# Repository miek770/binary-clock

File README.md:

# Binary Clock

This is a simple binary clock project using a PIC18F2220, pretty much for:

1. The fun of it;
2. Getting more experience with Eagle PCB design;
3. Doing a first PIC C project (I've only programmed PICs in assembly before).

The clamp on the right is there to hold down the buttons (hidden) while the glue dries up. More pictures in [media](https://github.com/miek770/binary-clock/tree/master/media)!

## To Do List

- Adjust timing to account for the cycles it takes for the time update and LED syncing. I noted an about 10 minutes drift over 24 hours, but I didn't take precise measurements at the beginning of the cycle. I just took another picture with my PC clock showing the seconds and the binary clock, and will compare the difference in at least 24 hours. I could also double-check by calculating the amount of cycles required for the interrupt subroutine;
    - Edit: This explaination is wrong; the timer doesn't stop counting while the ISR executes. I think the problem may be that I skip a "beat" because the ISR sometimes lasts longer than TMR0's 256 cycles counter. I'll see if the drift matches this assumption after a day.
- Test the low charge detection;
- Consider using delays.h instead of timer1 for the low-battery blink. The use of the timer seems unecessary and it would be a good excuse to explore the available functions;
- Consider importing timers.h to setup timer0, instead of manually setting each register;
- Consider using the idle power management mode when nothing is happening to reduce battery consumption. First check if it would interfere with timer0;

## Appearance

### Display

The clock uses 5 LEDs (bits) for the hours (24h format), 6 for the minutes and 6 for the seconds. Showing fractions of seconds seemed excessive.

## Supply

It can be fed either or by both:

1. 3x AA batteries;
2. A micro-USB port.

### Low Charge Detection

Both supplies are paralleled with diodes, and the PIC monitors the batteries' voltage so that an alarm (blinking LED) is raised when the batteries are low. For 1.5V AA batteries, this would be pretty much when they get under 1V. AN0 is used on the PIC to measure the battery voltage.

Hum thinking about it makes me realize that the voltage reference is Vdd. So if we ignore the voltage drop through the diode, which is gonna be constant, the voltage drop at the battery (with no USB supply) is going to drop proportionally with Vdd which means the AN0 measurement won't pick it up. Unless I use the voltage drop across the diode as a reference. At 4.5V at the batteries, with a 0.7V drop through the diode I'll get 3.8V at Vdd. When the batteries get to 3V (1V per cell), Vdd will equal 2.3V.

So Vbatt/Vdd = 4.5V/3.8V (1.184) at full charge, and 3V/2.3V (1.304) at low charge. Using a 50/50 voltage divider between Vbatt and AN0, the ratios would be 0.592 (full) and 0.652 (low). With a 10-bit A/D converter I have a 1024 resolution, which would be able to measure this. Basically the reading is going to go from 0/1023 to 1023/1023. A 0.592 ratio (full) would be read as 606 and a 0.652 ratio (low) as 667. So I could then consider any reading over 666 (0b1010011010) as a low battery charge.

This will need to be adjusted to account for the real diode voltage drop as well as the voltage divider ratio, but it should do the trick. For testing purposes I could use the time diodes to show the A/D conversion output. I have up to 17 bits (5+6+6 diodes).

## Timing

I switched from the PIC18F252 to the PIC18F2220 because the former doesn't have an internal oscillator. I assumed it did.

I will be using TMR0 to count seconds, using a bresenham algorithm as explained and implemented here: [http://www.romanblack.com/one_sec.htm](http://www.romanblack.com/one_sec.htm)

Basically (this is all from his website above):

    This next one is similar to the 1 second generators above. However it is optimised for speed and code space, because it uses a 16bit unsigned int variable for bres instead of a 32bit unsigned long. We do this by using values for the int period and the 1second period that are in the same ratio to each other, but smaller! We divide both values by 16;

    Optimised C code for a 1 second period with a 1MHz timer (4MHz xtal);

        // uses 1 variable; unsigned int bres
        // gets here every TMR0 int (every 256 ticks)

        bres += 16; // add (256/16) ticks to bresenham total

        if(bres >= 62500)   // if reached (1000000/16) 1 second!
        {
            bres -= 62500;  // subtract 1 second, retain error
            do_1sec_event();    // update clock, etc
        }

This is neat!

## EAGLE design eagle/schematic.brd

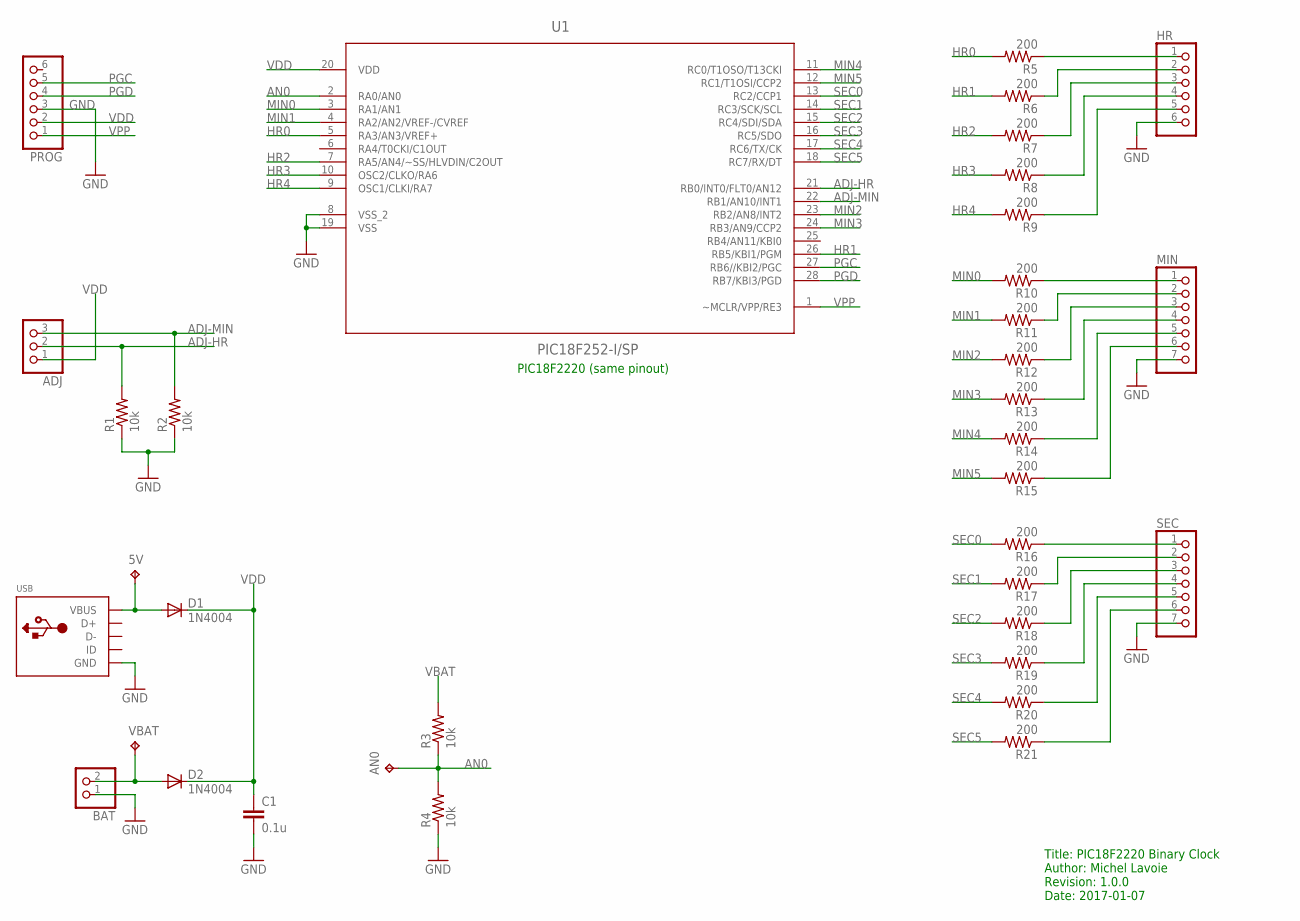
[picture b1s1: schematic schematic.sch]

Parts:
5V: TPPAD1-13; P1-13
ADJ: PINHD-1X3; 1X03
AN0: TPPAD1-13; P1-13
BAT: PINHD-1X2; 1X02
C1: 0.1u; CAP-PTH-SMALL-KIT
D1, D2: 1N4004; DO41-10
HR: PINHD-1X6; 1X06
MIN: PINHD-1X7; 1X07
PROG: PINHD-1X6; 1X06
R1, R2, R3, R4: 10k; AXIAL-0.3
R5, R6, R7, R8, R9, R10, R11, R12, R13, R14, R15, R16, R17, R18, R19, R20, R21: 200; AXIAL-0.3
SEC: PINHD-1X7; 1X07
U1: PIC18F252-I/SP; DIP254P762X508-28
USB: USBTHM; USB-MINIB-THM
VBAT: TPPAD1-13; P1-13

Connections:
5V: 5V.TP, D1.A, USB.VBUS
ADJ-HR: ADJ.2, R1.P$2 (2), U1.21 (RB0/INT0/FLT0/AN12)
ADJ-MIN: ADJ.3, R2.P$2 (2), U1.22 (RB1/AN10/INT1)
AN0: AN0.TP, R3.P$1 (1), R4.P$2 (2), U1.2 (RA0/AN0)
GND: BAT.1, C1.2, HR.6, MIN.7, PROG.3, R1.P$1 (1), R2.P$1 (1), R4.P$1 (1), SEC.7, U1.8 (VSS_2), U1.19 (VSS), USB.GND
HR0: R5.P$2 (2), U1.5 (RA3/AN3/VREF+)
HR1: R6.P$2 (2), U1.26 (RB5/KBI1/PGM)
HR2: R7.P$2 (2), U1.7 (RA5/AN4/~SS/HLVDIN/C2OUT)
HR3: R8.P$2 (2), U1.10 (OSC2/CLKO/RA6)
HR4: R9.P$2 (2), U1.9 (OSC1/CLKI/RA7)
MIN0: R10.P$2 (2), U1.3 (RA1/AN1)
MIN1: R11.P$2 (2), U1.4 (RA2/AN2/VREF-/CVREF)
MIN2: R12.P$2 (2), U1.23 (RB2/AN8/INT2)
MIN3: R13.P$2 (2), U1.24 (RB3/AN9/CCP2)
MIN4: R14.P$2 (2), U1.11 (RC0/T1OSO/T13CKI)
MIN5: R15.P$2 (2), U1.12 (RC1/T1OSI/CCP2)
unnamed: HR.1, R5.P$1 (1)
unnamed: HR.2, R6.P$1 (1)
unnamed: HR.3, R7.P$1 (1)
unnamed: HR.4, R8.P$1 (1)
unnamed: HR.5, R9.P$1 (1)
unnamed: MIN.1, R10.P$1 (1)
unnamed: MIN.2, R11.P$1 (1)
unnamed: MIN.3, R12.P$1 (1)
unnamed: MIN.4, R13.P$1 (1)
unnamed: MIN.5, R14.P$1 (1)
unnamed: MIN.6, R15.P$1 (1)
unnamed: R16.P$1 (1), SEC.1
unnamed: R17.P$1 (1), SEC.2
unnamed: R18.P$1 (1), SEC.3
unnamed: R19.P$1 (1), SEC.4
unnamed: R20.P$1 (1), SEC.5
unnamed: R21.P$1 (1), SEC.6
PGC: PROG.5, U1.27 (RB6//KBI2/PGC)
PGD: PROG.4, U1.28 (RB7/KBI3/PGD)
SEC0: R16.P$2 (2), U1.13 (RC2/CCP1)
SEC1: R17.P$2 (2), U1.14 (RC3/SCK/SCL)
SEC2: R18.P$2 (2), U1.15 (RC4/SDI/SDA)
SEC3: R19.P$2 (2), U1.16 (RC5/SDO)
SEC4: R20.P$2 (2), U1.17 (RC6/TX/CK)
SEC5: R21.P$2 (2), U1.18 (RC7/RX/DT)
VBAT: BAT.2, D2.A, R3.P$2 (2), VBAT.TP
VDD: ADJ.1, C1.1, D1.C, D2.C, PROG.2, U1.20 (VDD)
VPP: PROG.1, U1.1 (~MCLR/VPP/RE3)

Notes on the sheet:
Title: PIC18F2220 Binary Clock Author: Michel Lavoie Revision: 1.0.0 Date: 2017-01-07
PIC18F2220 (same pinout)

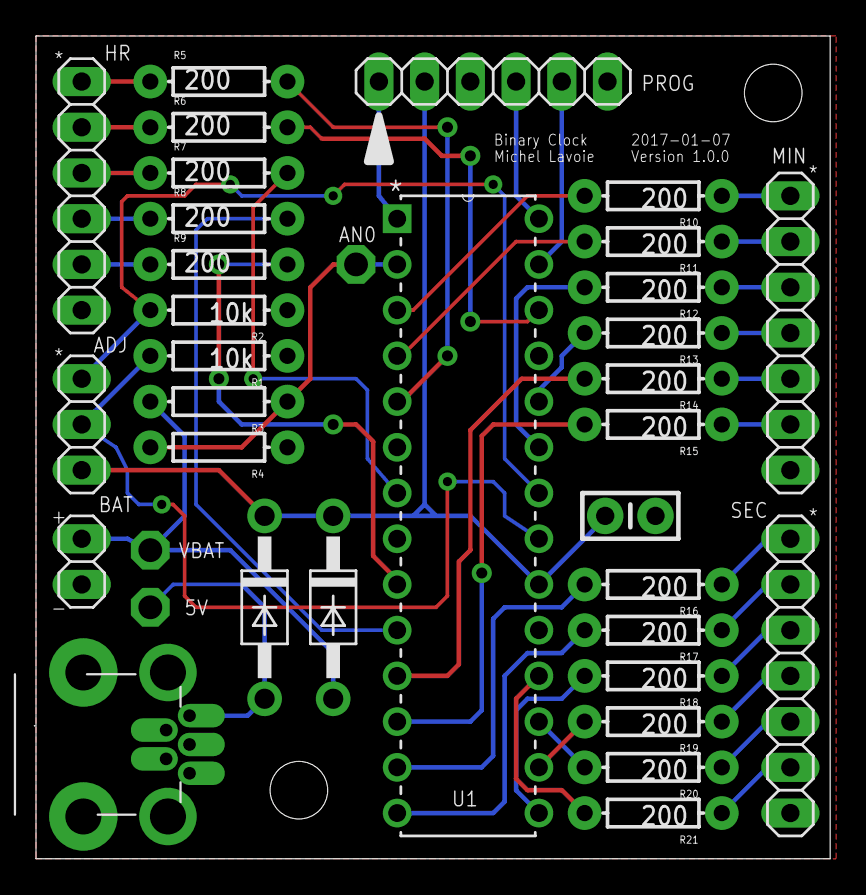
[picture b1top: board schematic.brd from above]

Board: 2 copper layers, 44.1 x 45.7 mm, 35 parts (0 on the bottom side), 44 nets.

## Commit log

2016-11-26 New schematic
2016-11-27 PCB in progress
2016-11-27 PCB completed
2016-11-27 Added OSH Park render
2016-11-27 Added schema image
2016-11-27 Rewrote README, and added to-do-list based on OSH Park's images of version 0.1.0
2016-11-27 Added C stuff to ignore
2016-11-27 Updated To Do list
2016-11-27 Interrupts for adjustments
2016-11-27 Version 0.1.1. Applied all items in the To Do list.
2016-11-27 Updated To Do.
2016-11-27 Added test (for ssh key)
2016-11-27 Removed test
2016-11-27 Adjusted title font size. Order sent to OSH Park.
2016-11-28 Updated To Do List, again.
2016-11-29 Changed PIC18F252 for PIC18F2220, the former has no internal oscillator.
2016-11-29 PIC configuration in progress, timing algorithm found.
2016-11-30 Configuration and timing interrupt in progress... duty calls.
2016-12-01 A/D configuration and basic interrupt.
2016-12-01 Method for voltage measurement.
2016-12-02 Seem to have finished the code, but can't test it without the PCB (or a test circuit).
2016-12-02 Removed unecessary code, updated to-do list.
2016-12-02 Noted to switch from 4 to 3 AA batteries.
2016-12-02 Added time adjustment interrupts.
2016-12-02 Changed from 4x AA to 3x AA batteries.
2016-12-04 Added task; front panel appearance.
2016-12-04 Other items in todo.
2016-12-04 Shortened while loop.
2016-12-04 Various enhancements per C18 User's Guide.
2016-12-04 Other tips and notes.
2016-12-04 Code reorganisation.
2016-12-04 Removed 'near' qualifier, it raised error 1303. Not sure why.
2016-12-04 Fixed the issue with 'near' qualifier.
2016-12-04 Replaced PORT with LAT for digital outputs.
2016-12-04 Adjusted todo list per latest commit.
2016-12-31 Debugging sync_leds()
2016-12-31 Added bit shifts
2016-12-31 Modified the bit shifts to make it cleaner
2016-12-31 Added function get_bit()
2016-12-31 Clock now working, the 'save=...' isn't required with volatiles
2016-12-31 Removed obsolete notes
2017-01-04 Added a few things to debug
2017-01-06 further debugging for RA4 (pin 6, hour bit 1)
2017-01-07 Corrigé les bugs restants, mis à jour la documentation
2017-01-07 Added picture to README
2017-01-08 Added note to correct time drift cause by ISR execution
2017-01-08 Added further notes regarding time drift, as well as new theory
2017-01-10 Calculated time shift
2017-01-10 Switched to 16-bit timer
2017-01-22 Added +8.06% frequency shift
2017-01-22 I meant 0.8%

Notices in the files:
parts and their libraries:
SparkFun-Capacitors: Licensing: Creative Commons ShareAlike 4.0 International - https://creativecommons.org/licenses/by-sa/4.0
